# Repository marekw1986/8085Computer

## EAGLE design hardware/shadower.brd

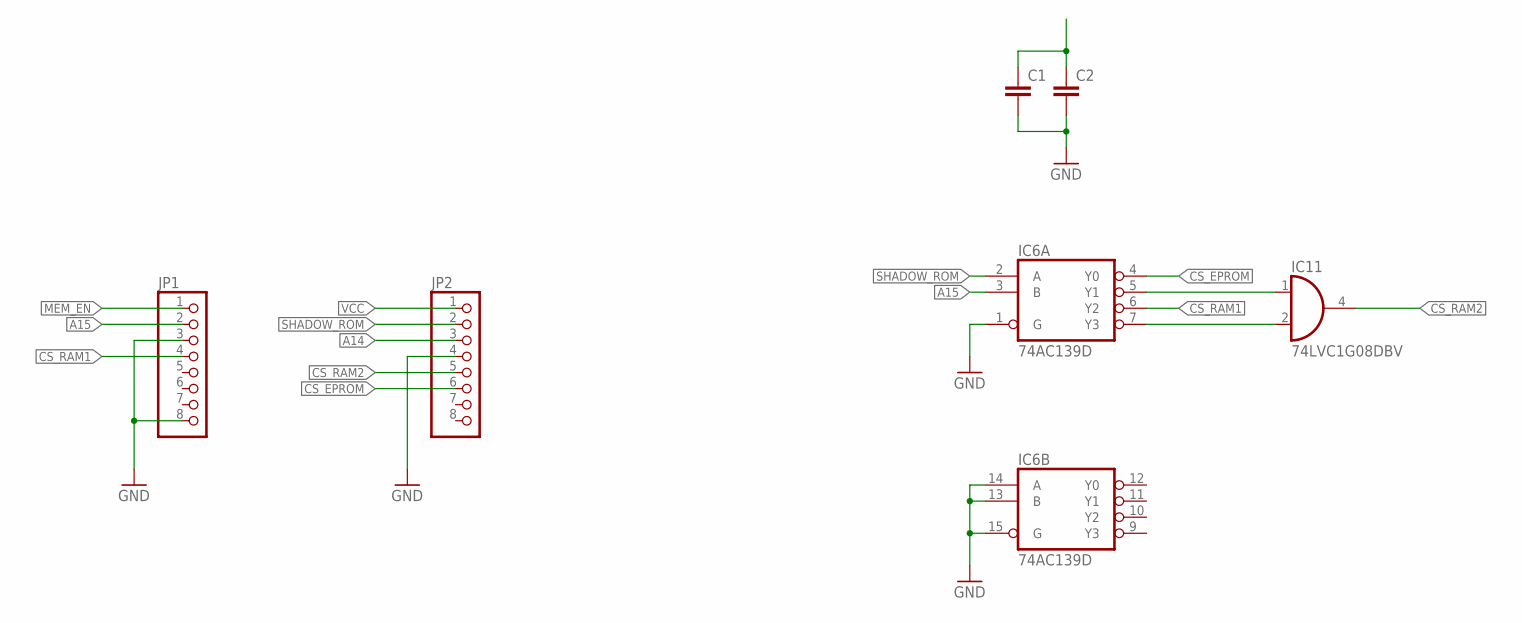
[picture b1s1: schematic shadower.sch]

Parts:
C1, C2: C-EUC0603; C0603
IC6: 74AC139D; SO16
IC11: 74LVC1G08DBV; SOT23-5
JP1, JP2: PINHD-1X8; 1X08

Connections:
A14: JP2.3
A15: IC6.3 (B), JP1.2
CS_EPROM: IC6.4 (Y0), JP2.6
CS_RAM1: IC6.6 (Y2), JP1.4
CS_RAM2: IC11.4 (O), JP2.5
GND: C1.2, C2.2, IC6.1 (G), IC6.8 (GND), IC6.13 (B), IC6.14 (A), IC6.15 (G), IC11.3 (GND), JP1.3, JP1.8, JP2.4
MEM_EN: JP1.1
unnamed: IC6.5 (Y1), IC11.1 (I0)
unnamed: IC6.7 (Y3), IC11.2 (I1)
SHADOW_ROM: IC6.2 (A), JP2.2
VCC: C1.1, C2.1, IC6.16 (VCC), IC11.5 (VCC), JP2.1

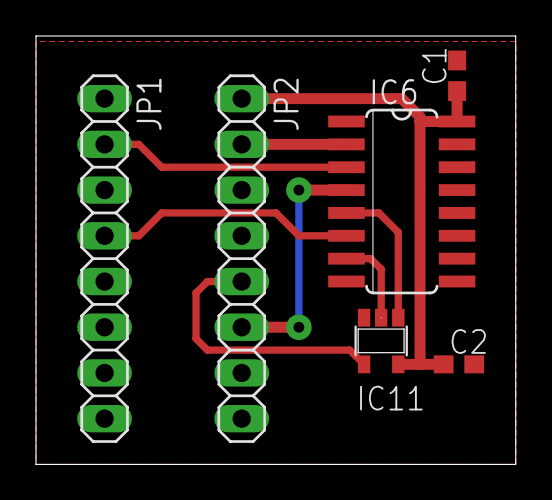
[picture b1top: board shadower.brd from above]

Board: 2 copper layers, 26.6 x 23.8 mm, 6 parts (0 on the bottom side), 9 nets.

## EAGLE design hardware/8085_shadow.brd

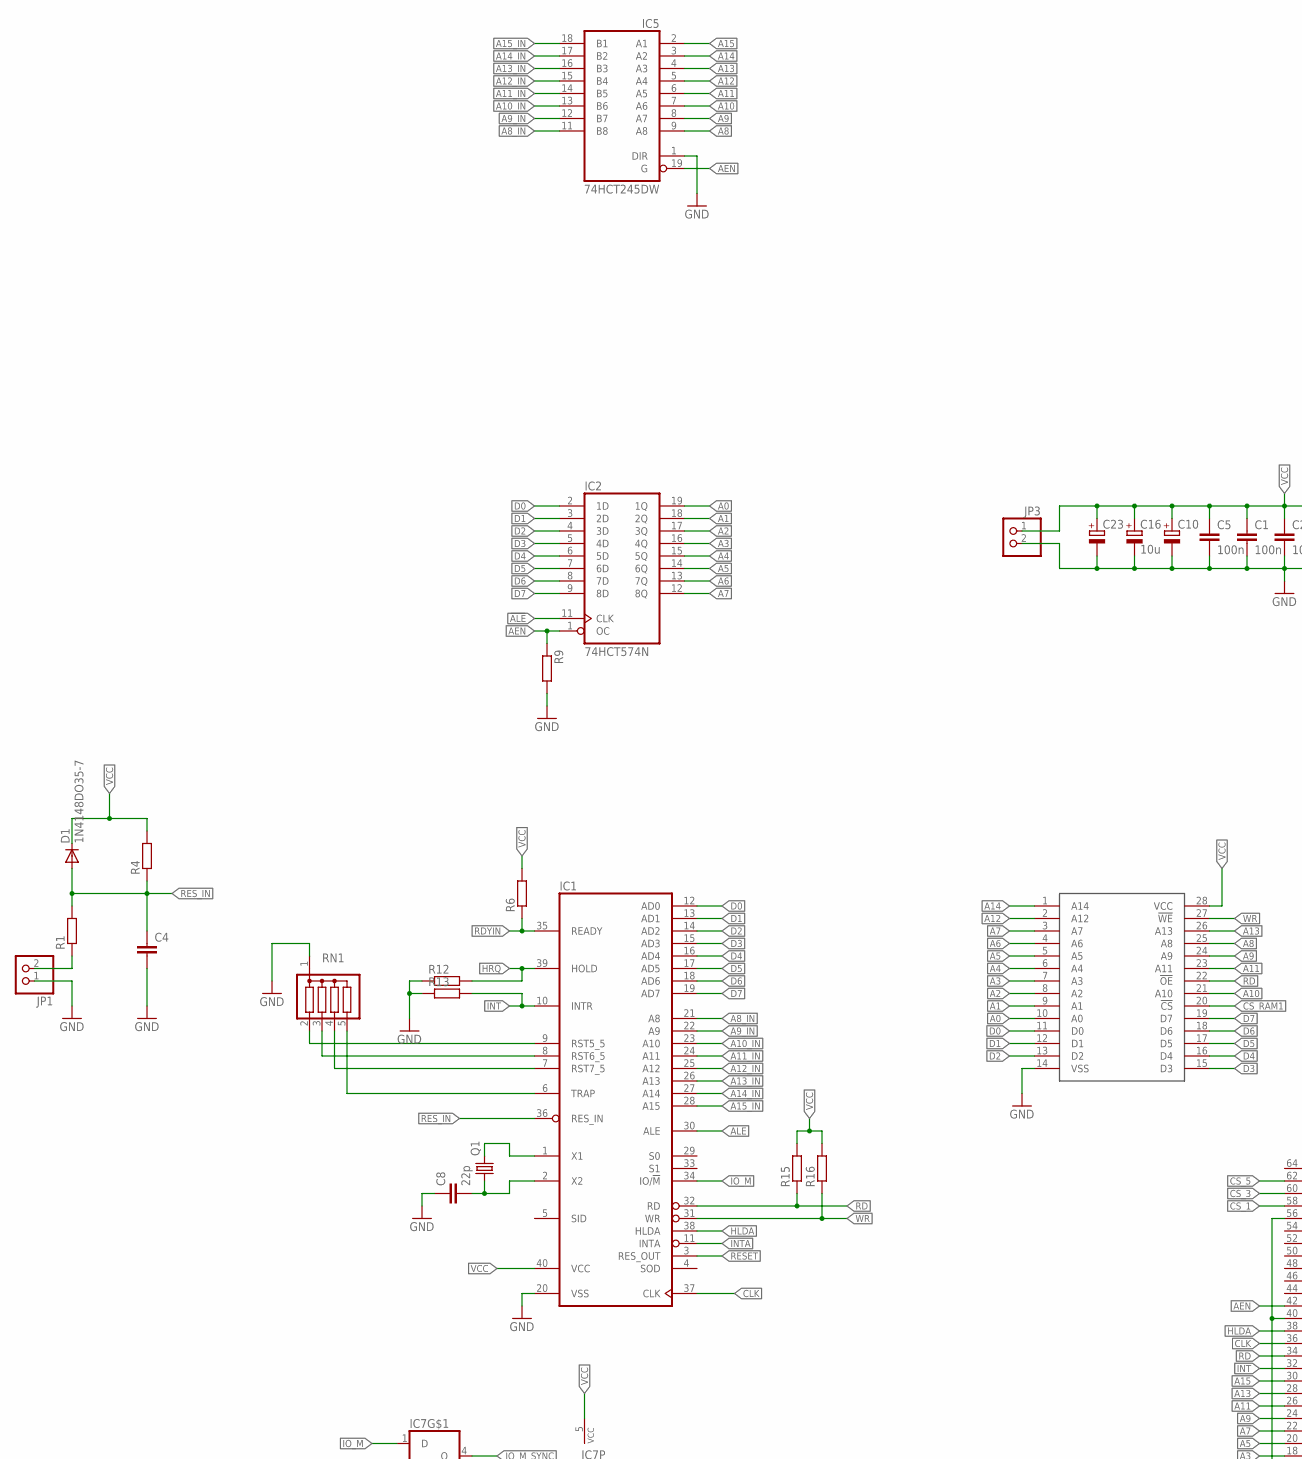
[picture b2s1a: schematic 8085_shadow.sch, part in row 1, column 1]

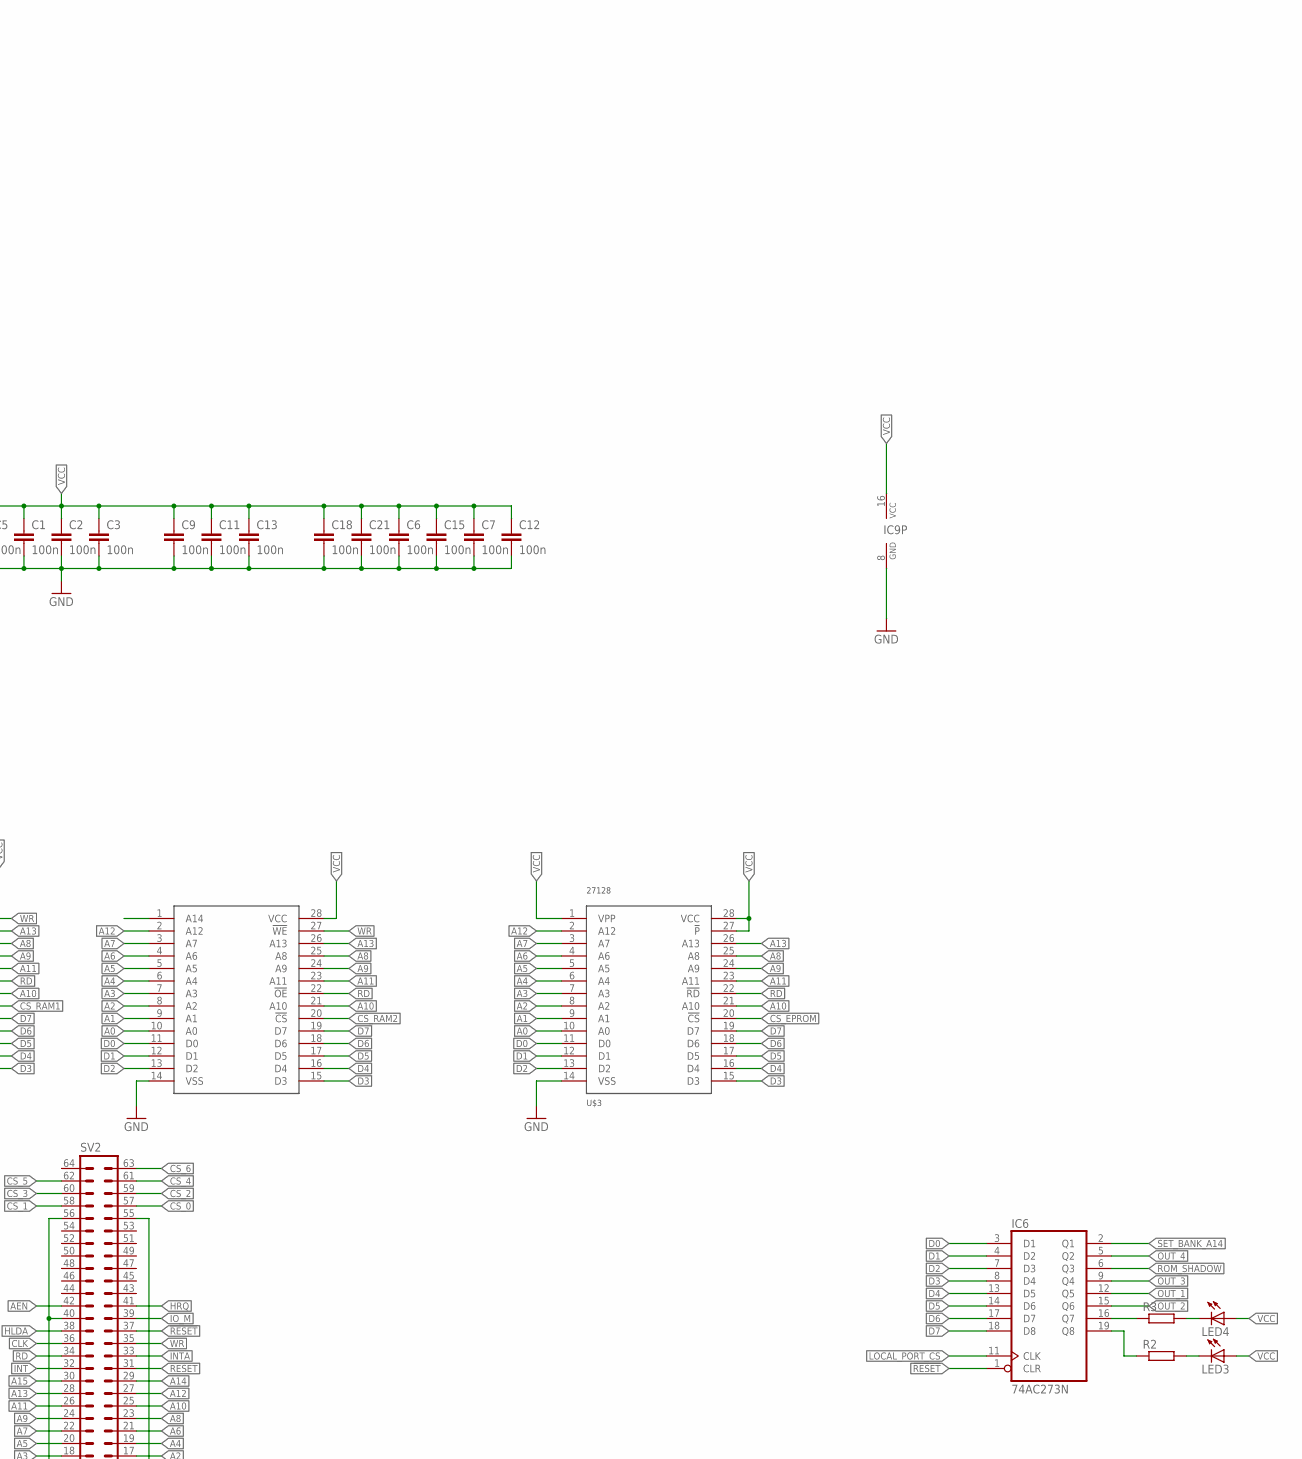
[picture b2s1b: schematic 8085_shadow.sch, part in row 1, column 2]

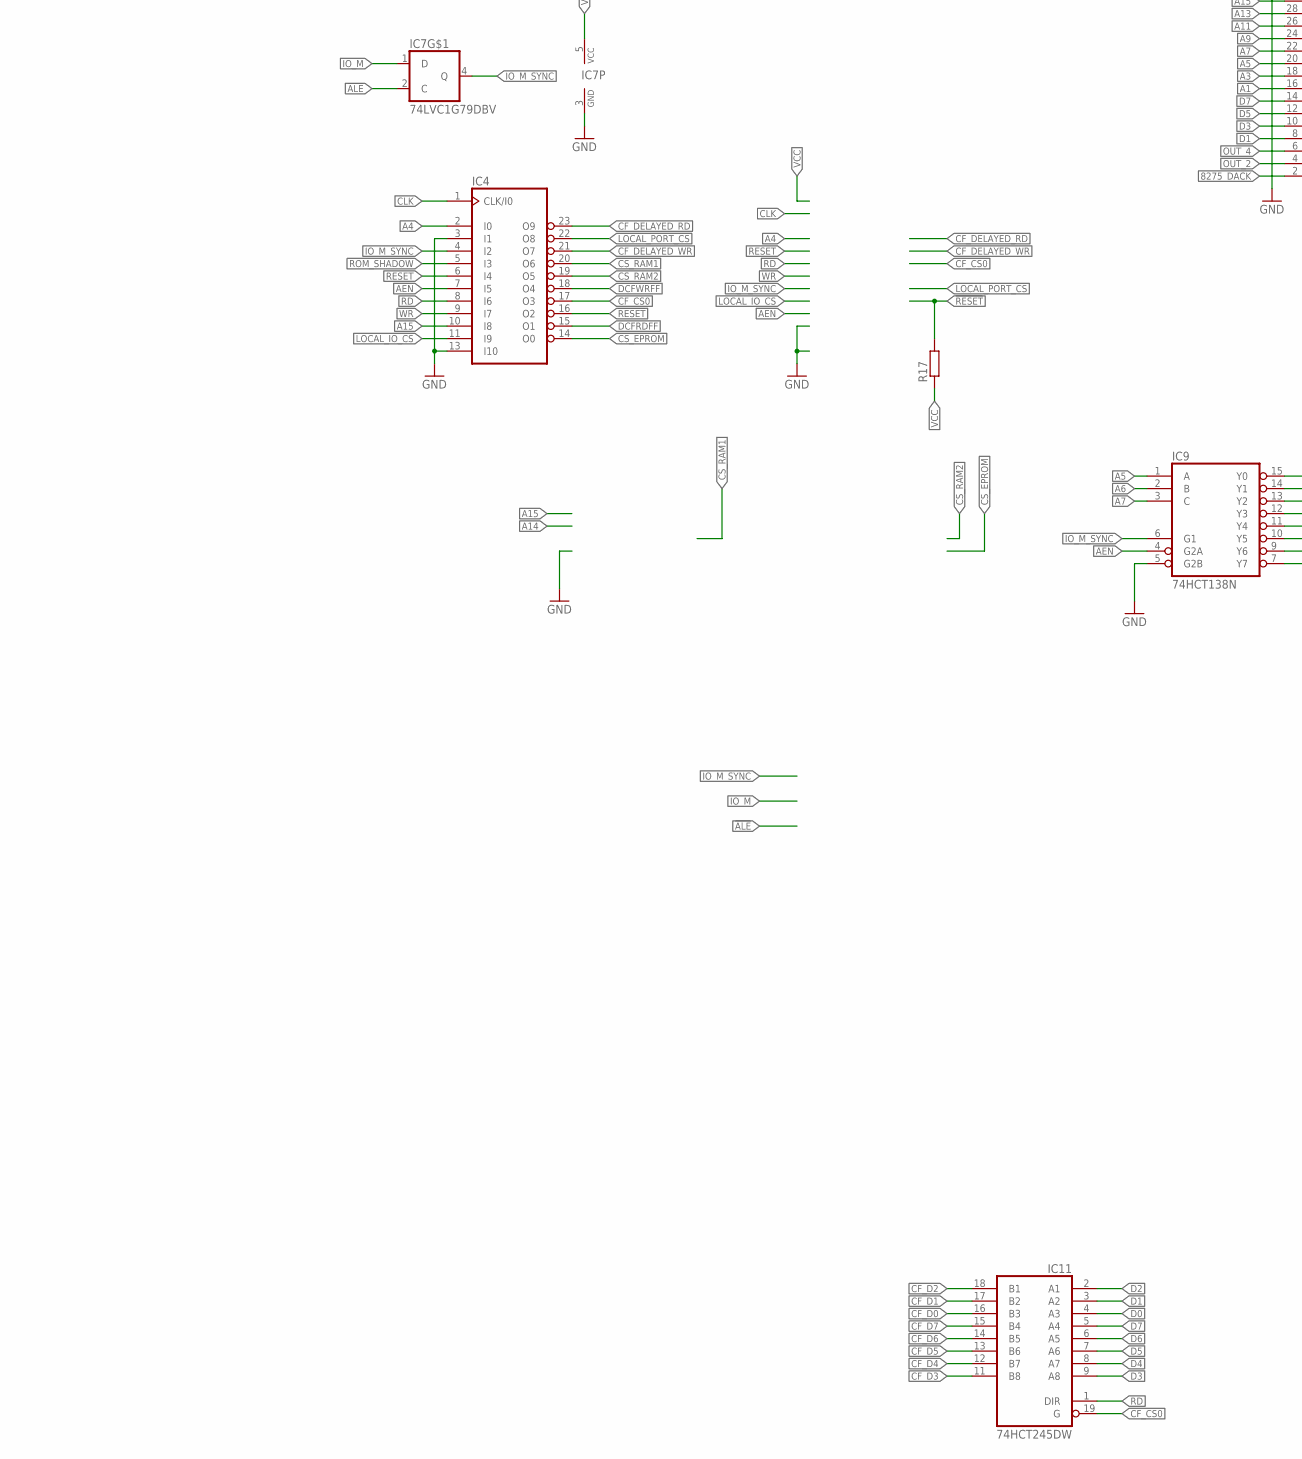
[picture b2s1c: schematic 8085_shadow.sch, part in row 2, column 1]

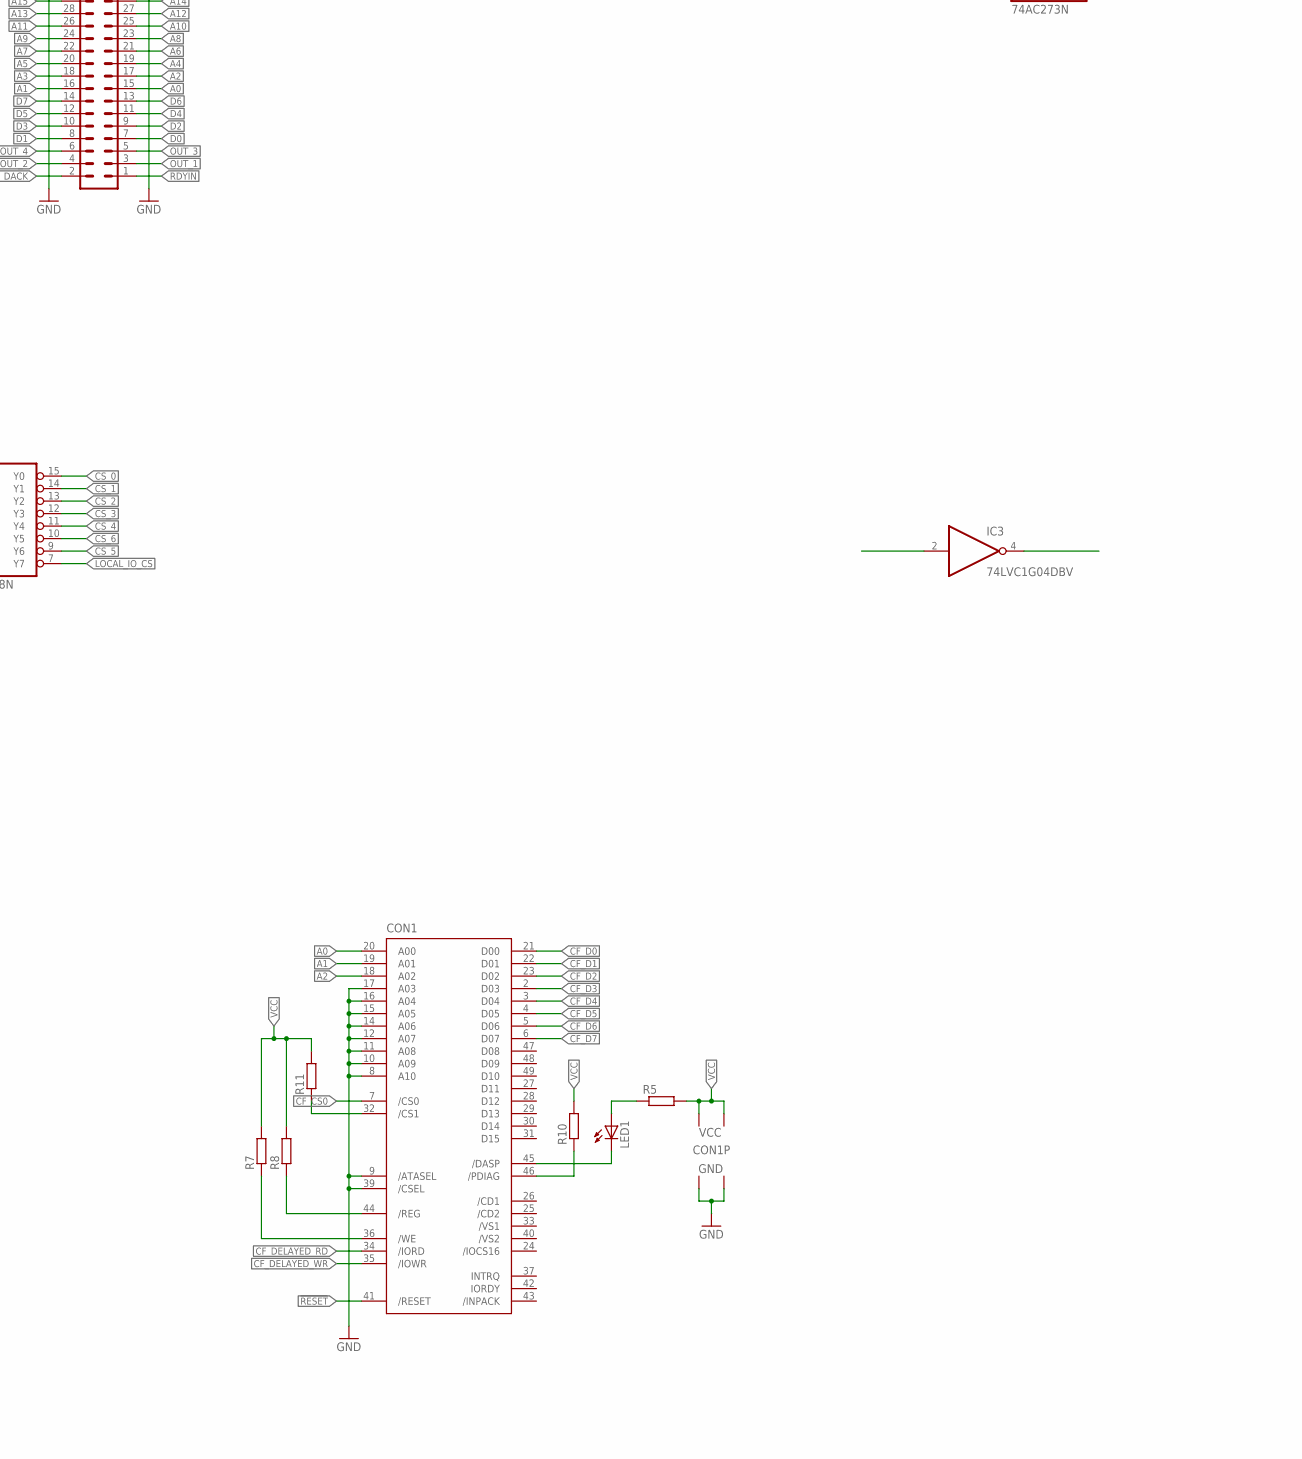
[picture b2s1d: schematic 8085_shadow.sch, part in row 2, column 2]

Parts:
C1, C2, C3, C11, C12, C13: 100n; C0805
C4: C-EUC0603; C0603
C5, C6, C7, C15, C18, C21: 100n; C0603
C8: 22p; C0603
C9: 100n; C1206
C10, C23: CPOL-EUE5-10.5; E5-10,5
C16: 10u; SMC_B
CON1: CF-CARD-IDE_MODE; MI20-50PD-SF
D1: 1N4148DO35-7; DO35-7
IC1: 8085; DIL40
IC2: 74HCT574N; DIL20
IC3: 74LVC1G04DBV; SOT23-5
IC4: 22V10; DIL24-3
IC5, IC11: 74HCT245DW; SO20W
IC6: 74AC273N; DIL20
IC7: 74LVC1G79DBV; SOT23-5
IC9: 74HCT138N; DIL16
JP1, JP3: PINHD-1X2; 1X02
LED1, LED3, LED4: LED5MM
Q1: CRYSTALHC49S; HC49/S
R1, R6: R-EU_0204/5; 0204/5
R2, R3: R-EU_R1206; R1206
R4, R15, R16, R17: R-EU_0204/7; 0204/7
R5, R9, R12, R13: R-EU_R0603; R0603
R7, R11: R-EU_0207/10; 0207/10
R8, R10: R-EU_0207/12; 0207/12
RN1: G04R; SIL5
SV2: ML64L
U$2, U$4: 62256; DIL28-6
U$3: 27128; DIL28

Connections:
8275_DACK: SV2.2
!ALE: IC2.11 (CLK), IC3.4 (O), IC7.2 (C)
!RESET: CON1.41 (/RESET), IC4.16 (O2), IC6.1 (CLR), R17.2, SV2.37
A0: CON1.20 (A00), IC2.19 (1Q), SV2.15, U$2.10 (A0), U$3.10 (A0), U$4.10 (A0)
A1: CON1.19 (A01), IC2.18 (2Q), SV2.16, U$2.9 (A1), U$3.9 (A1), U$4.9 (A1)
A2: CON1.18 (A02), IC2.17 (3Q), SV2.17, U$2.8 (A2), U$3.8 (A2), U$4.8 (A2)
A3: IC2.16 (4Q), SV2.18, U$2.7 (A3), U$3.7 (A3), U$4.7 (A3)
A4: IC2.15 (5Q), IC4.2 (I0), SV2.19, U$2.6 (A4), U$3.6 (A4), U$4.6 (A4)
A5: IC2.14 (6Q), IC9.1 (A), SV2.20, U$2.5 (A5), U$3.5 (A5), U$4.5 (A5)
A6: IC2.13 (7Q), IC9.2 (B), SV2.21, U$2.4 (A6), U$3.4 (A6), U$4.4 (A6)
A7: IC2.12 (8Q), IC9.3 (C), SV2.22, U$2.3 (A7), U$3.3 (A7), U$4.3 (A7)
A8: IC5.9 (A8), SV2.23, U$2.25 (A8), U$3.25 (A8), U$4.25 (A8)
A8_IN: IC1.21 (A8), IC5.11 (B8)
A9: IC5.8 (A7), SV2.24, U$2.24 (A9), U$3.24 (A9), U$4.24 (A9)
A9_IN: IC1.22 (A9), IC5.12 (B7)
A10: IC5.7 (A6), SV2.25, U$2.21 (A10), U$3.21 (A10), U$4.21 (A10)
A10_IN: IC1.23 (A10), IC5.13 (B6)
A11: IC5.6 (A5), SV2.26, U$2.23 (A11), U$3.23 (A11), U$4.23 (A11)
A11_IN: IC1.24 (A11), IC5.14 (B5)
A12: IC5.5 (A4), SV2.27, U$2.2 (A12), U$3.2 (A12), U$4.2 (A12)
A12_IN: IC1.25 (A12), IC5.15 (B4)
A13: IC5.4 (A3), SV2.28, U$2.26 (A13), U$3.26 (A13), U$4.26 (A13)
A13_IN: IC1.26 (A13), IC5.16 (B3)
A14: IC5.3 (A2), SV2.29, U$2.1 (A14), U$4.1 (A14)
A14_IN: IC1.27 (A14), IC5.17 (B2)
A15: IC4.10 (I8), IC5.2 (A1), SV2.30
A15_IN: IC1.28 (A15), IC5.18 (B1)
AEN: IC2.1 (OC), IC4.7 (I5), IC5.19 (G), IC9.4 (G2A), R9.1, SV2.42
ALE: IC1.30 (ALE), IC3.2 (I)
CF_CS0: CON1.7 (/CS0), IC4.17 (O3), IC11.19 (G)
CF_D0: CON1.21 (D00), IC11.16 (B3)
CF_D1: CON1.22 (D01), IC11.17 (B2)
CF_D2: CON1.23 (D02), IC11.18 (B1)
CF_D3: CON1.2 (D03), IC11.11 (B8)
CF_D4: CON1.3 (D04), IC11.12 (B7)
CF_D5: CON1.4 (D05), IC11.13 (B6)
CF_D6: CON1.5 (D06), IC11.14 (B5)
CF_D7: CON1.6 (D07), IC11.15 (B4)
CF_DELAYED_RD: CON1.34 (/IORD), IC4.23 (O9)
CF_DELAYED_WR: CON1.35 (/IOWR), IC4.21 (O7)
CLK: IC1.37 (CLK), IC4.1 (CLK/I0), SV2.36
CS_0: IC9.15 (Y0), SV2.57
CS_1: IC9.14 (Y1), SV2.58
CS_2: IC9.13 (Y2), SV2.59
CS_3: IC9.12 (Y3), SV2.60
CS_4: IC9.11 (Y4), SV2.61
CS_5: IC9.9 (Y6), SV2.62
CS_6: IC9.10 (Y5), SV2.63
CS_EPROM: IC4.14 (O0), U$3.20 (!CS)
CS_RAM1: IC4.20 (O6), U$4.20 (!CS)
CS_RAM2: IC4.19 (O5), U$2.20 (!CS)
D0: IC1.12 (AD0), IC2.2 (1D), IC6.3 (D1), IC11.4 (A3), SV2.7, U$2.11 (D0), U$3.11 (D0), U$4.11 (D0)
D1: IC1.13 (AD1), IC2.3 (2D), IC6.4 (D2), IC11.3 (A2), SV2.8, U$2.12 (D1), U$3.12 (D1), U$4.12 (D1)
D2: IC1.14 (AD2), IC2.4 (3D), IC6.7 (D3), IC11.2 (A1), SV2.9, U$2.13 (D2), U$3.13 (D2), U$4.13 (D2)
D3: IC1.15 (AD3), IC2.5 (4D), IC6.8 (D4), IC11.9 (A8), SV2.10, U$2.15 (D3), U$3.15 (D3), U$4.15 (D3)
D4: IC1.16 (AD4), IC2.6 (5D), IC6.13 (D5), IC11.8 (A7), SV2.11, U$2.16 (D4), U$3.16 (D4), U$4.16 (D4)
D5: IC1.17 (AD5), IC2.7 (6D), IC6.14 (D6), IC11.7 (A6), SV2.12, U$2.17 (D5), U$3.17 (D5), U$4.17 (D5)
D6: IC1.18 (AD6), IC2.8 (7D), IC6.17 (D7), IC11.6 (A5), SV2.13, U$2.18 (D6), U$3.18 (D6), U$4.18 (D6)
D7: IC1.19 (AD7), IC2.9 (8D), IC6.18 (D8), IC11.5 (A4), SV2.14, U$2.19 (D7), U$3.19 (D7), U$4.19 (D7)
DCFRDFF: IC4.15 (O1)
DCFWRFF: IC4.18 (O4)
GND: C1.2, C2.2, C3.2, C4.2, C5.2, C6.2, C7.2, C8.1, C9.2, C10.-, C11.2, C12.2, C13.2, C15.2, C16.-, C18.2, C21.2, C23.-, CON1.1 (GND1), CON1.8 (A10), CON1.9 (/ATASEL), CON1.10 (A09), CON1.11 (A08), CON1.12 (A07), CON1.14 (A06), CON1.15 (A05), CON1.16 (A04), CON1.17 (A03), CON1.39 (/CSEL), CON1.50 (GND2), IC1.20 (VSS), IC2.10 (GND), IC3.3 (GND), IC4.3 (I1), IC4.12 (GND), IC4.13 (I10), IC5.1 (DIR), IC5.10 (GND), IC6.10 (GND), IC7.3 (GND), IC9.5 (G2B), IC9.8 (GND), IC11.10 (GND), JP1.1, JP3.2, R9.2, R12.1, R13.1, RN1.1, SV2.40, SV2.55, SV2.56, U$2.14 (VSS), U$3.14 (VSS), U$4.14 (VSS)
HLDA: IC1.38 (HLDA), SV2.38
HRQ: IC1.39 (HOLD), R12.2, SV2.41
INT: IC1.10 (INTR), R13.2, SV2.32
INTA: IC1.11 (INTA), SV2.33
IO_M: IC1.34 (IO/!M), IC7.1 (D), SV2.39
IO_M_SYNC: IC4.4 (I2), IC7.4 (Q), IC9.6 (G1)
LOCAL_IO_CS: IC4.11 (I9), IC9.7 (Y7)
LOCAL_PORT_CS: IC4.22 (O8), IC6.11 (CLK)
unnamed: IC1.1 (X1), Q1.2
unnamed: C8.2, IC1.2 (X2), Q1.1
unnamed: IC1.9 (RST5_5), RN1.2
unnamed: IC1.8 (RST6_5), RN1.3
unnamed: IC6.16 (Q7), R3.1
unnamed: IC1.7 (RST7_5), RN1.4
unnamed: IC1.6 (TRAP), RN1.5
unnamed: LED3.K (C), R2.2
unnamed: LED4.K (C), R3.2
unnamed: IC6.19 (Q8), R2.1
unnamed: CON1.44 (/REG), R8.1
unnamed: CON1.36 (/WE), R7.1
unnamed: CON1.46 (/PDIAG), R10.1
unnamed: JP1.2, R1.1
unnamed: LED1.A, R5.1
unnamed: CON1.45 (/DASP), LED1.K (C)
unnamed: CON1.32 (/CS1), R11.1
OUT_1: IC6.12 (Q5), SV2.3
OUT_2: IC6.15 (Q6), SV2.4
OUT_3: IC6.9 (Q4), SV2.5
OUT_4: IC6.5 (Q2), SV2.6
RD: IC1.32 (RD), IC4.8 (I6), IC11.1 (DIR), R15.1, SV2.34, U$2.22 (!OE), U$3.22 (!RD), U$4.22 (!OE)
RDYIN: IC1.35 (READY), R6.1, SV2.1
RESET: IC1.3 (RES_OUT), IC4.6 (I4), SV2.31
RES_IN: C4.1, D1.A, IC1.36 (RES_IN), R1.2, R4.1
ROM_SHADOW: IC4.5 (I3), IC6.6 (Q3)
SET_BANK_A14: IC6.2 (Q1)
VCC: C1.1, C2.1, C3.1, C5.1, C6.1, C7.1, C9.1, C10.+, C11.1, C12.1, C13.1, C15.1, C16.+, C18.1, C21.1, C23.+, CON1.13 (VCC2), CON1.38 (VCC1), D1.C, IC1.40 (VCC), IC2.20 (VCC), IC3.5 (VCC), IC4.24 (VCC), IC5.20 (VCC), IC6.20 (VCC), IC7.5 (VCC), IC9.16 (VCC), IC11.20 (VCC), JP3.1, LED3.A, LED4.A, R4.2, R5.2, R6.2, R7.2, R8.2, R10.2, R11.2, R15.2, R16.2, R17.1, U$2.28 (VCC), U$3.1 (VPP), U$3.27 (!P), U$3.28 (VCC), U$4.28 (VCC)
WR: IC1.31 (WR), IC4.9 (I7), R16.1, SV2.35, U$2.27 (!WE), U$4.27 (!WE)

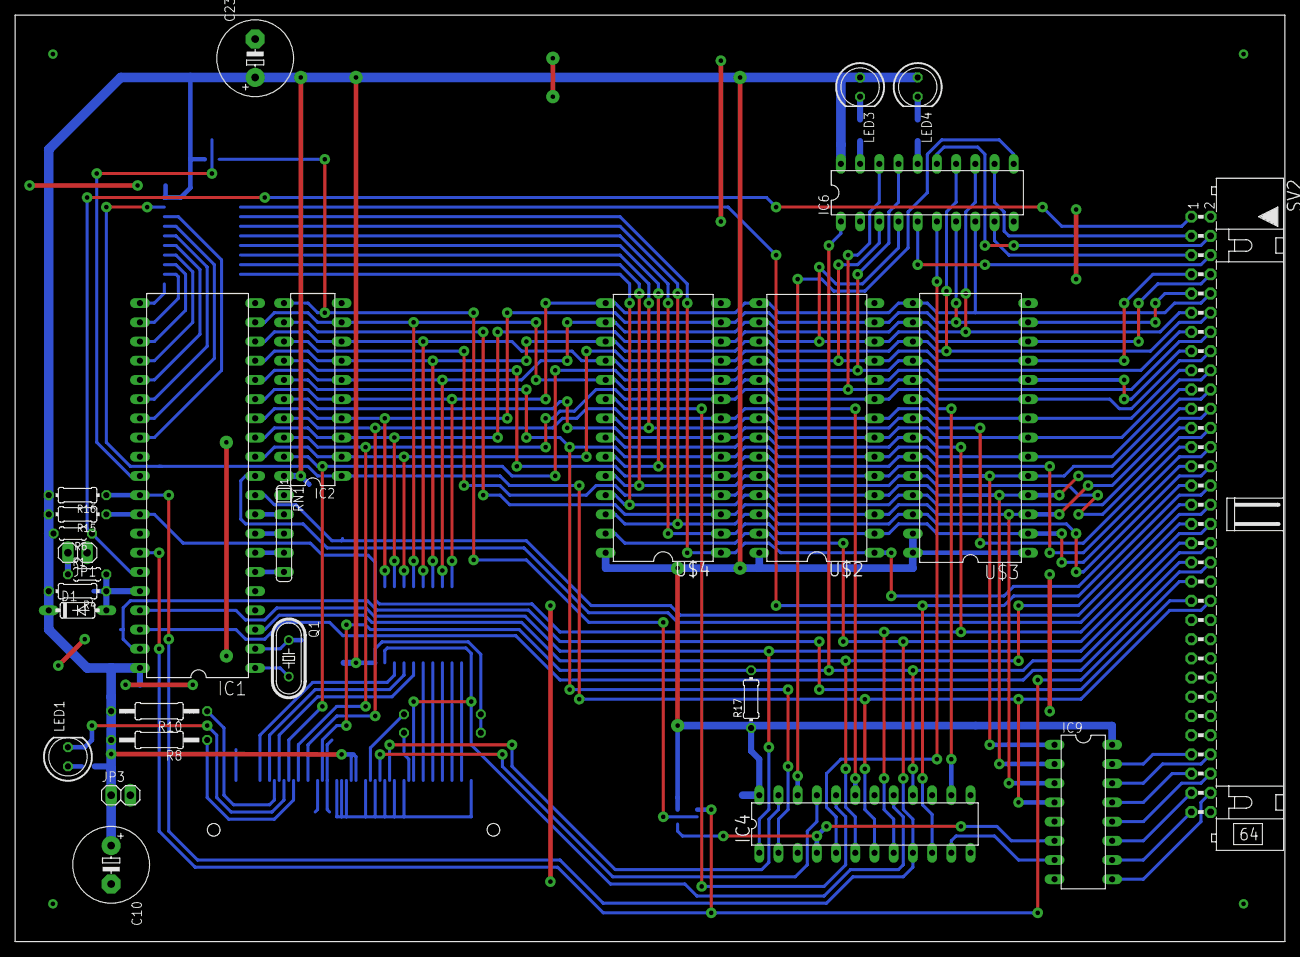
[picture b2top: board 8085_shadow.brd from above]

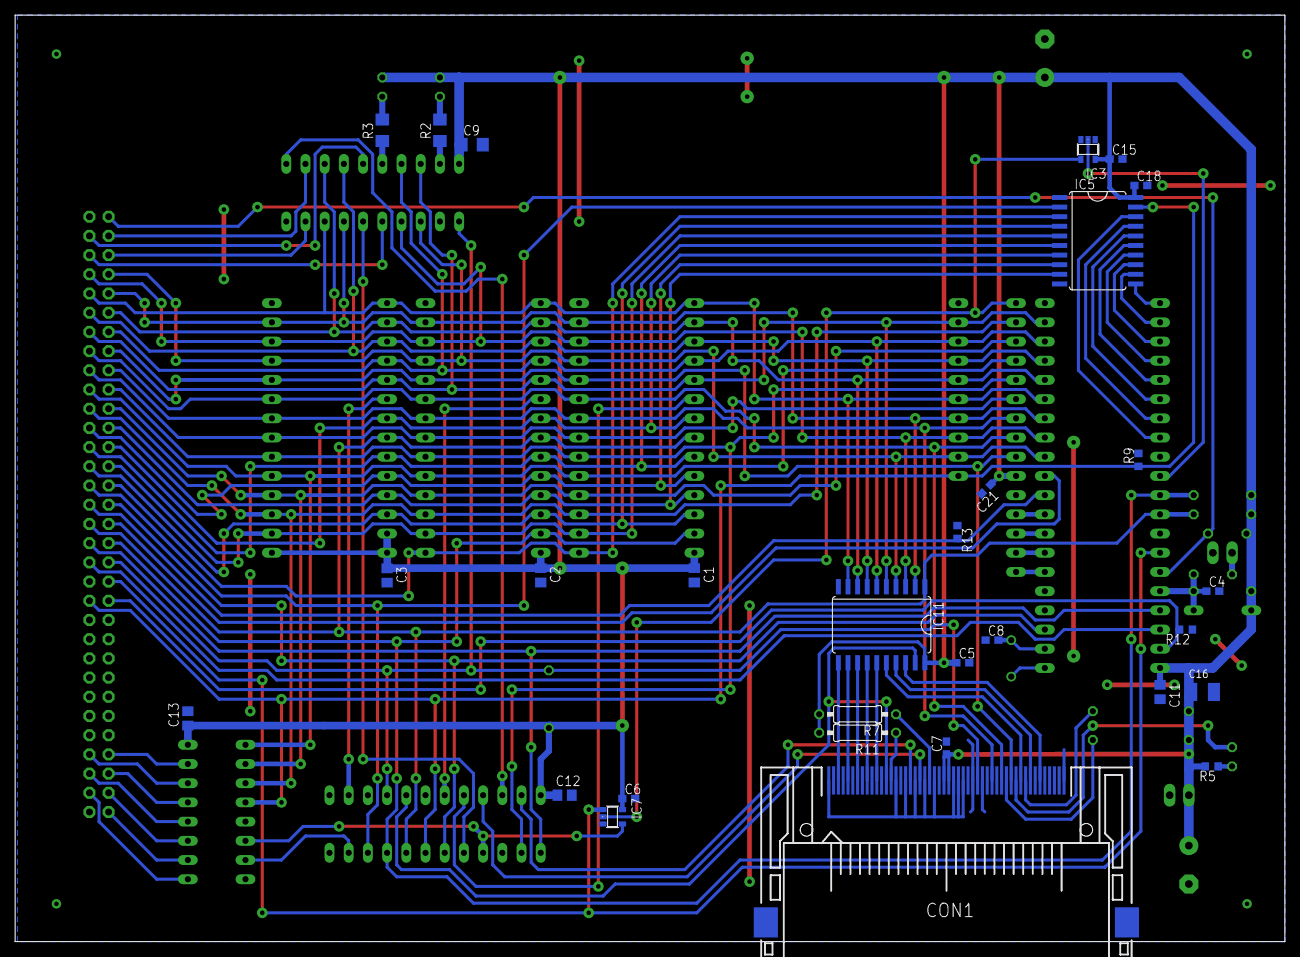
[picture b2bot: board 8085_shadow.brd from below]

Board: 2 copper layers, 167.9 x 122.5 mm, 56 parts (29 on the bottom side), 95 nets.

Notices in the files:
parts and their libraries:
SparkFun-Connectors: Licensing: Creative Commons ShareAlike 4.0 International - https://creativecommons.org/licenses/by-sa/4.0
